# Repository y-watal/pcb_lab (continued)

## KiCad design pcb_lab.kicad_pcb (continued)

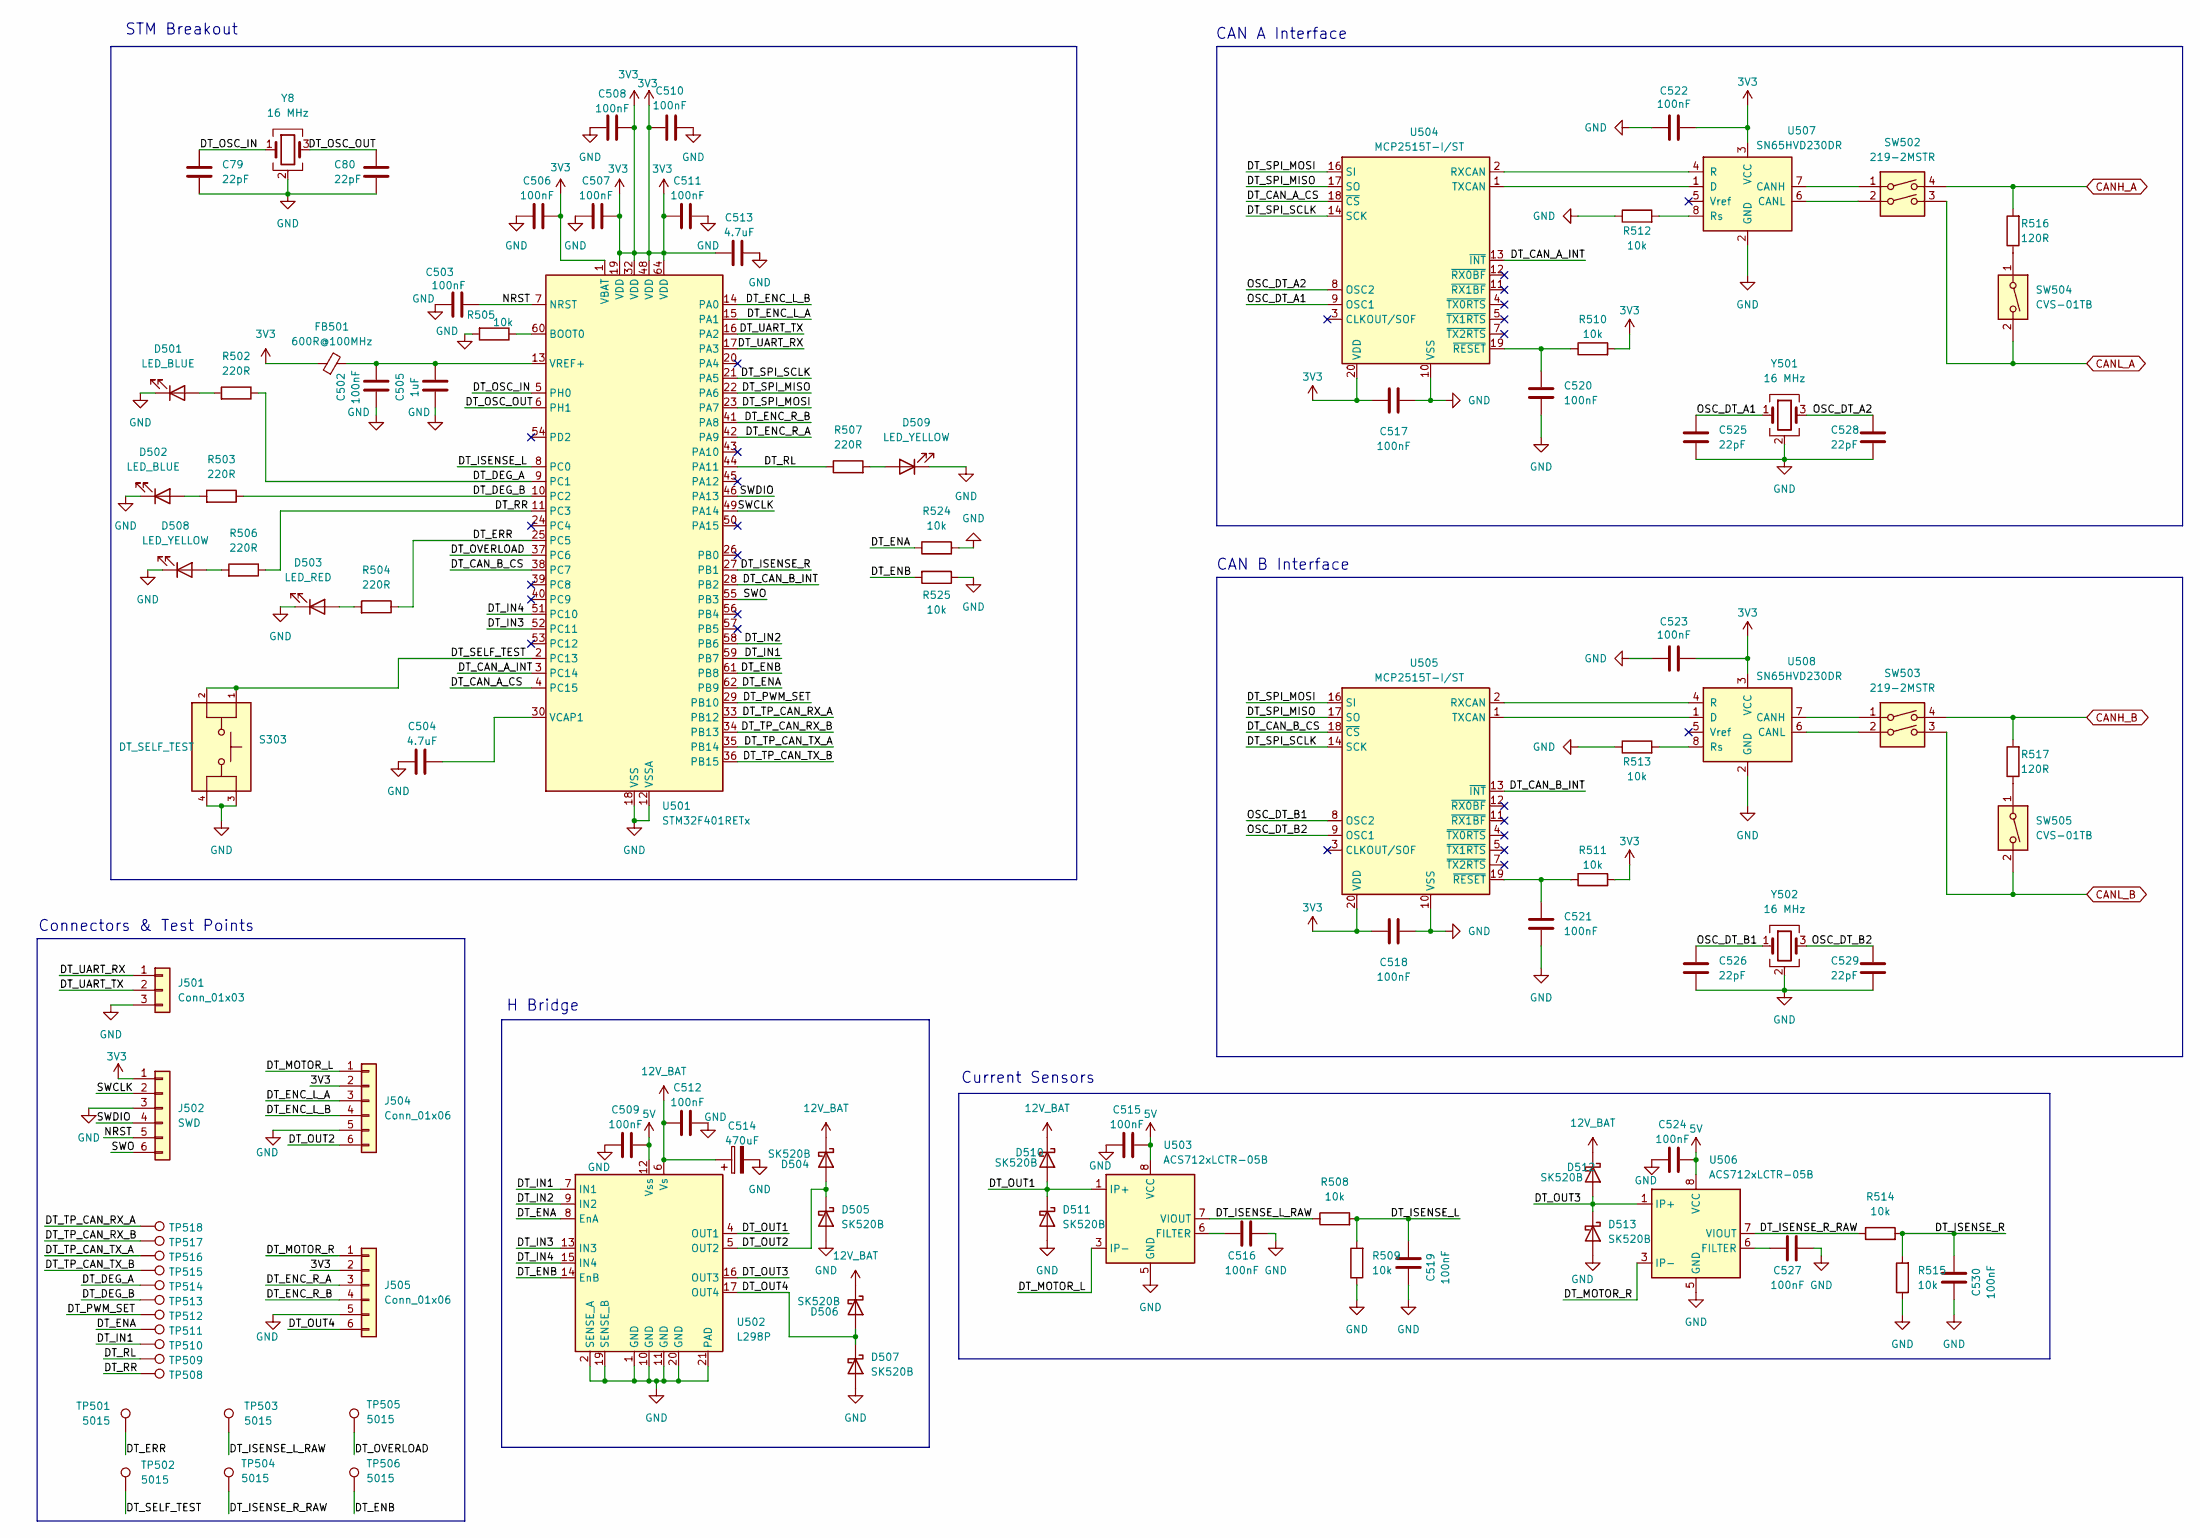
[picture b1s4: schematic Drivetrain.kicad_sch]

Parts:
C79, C80, C525, C526, C528, C529: 22pF; C_0603_1608Metric; Manufacturer Part Number C0603C220J1GACTU; LCSC Part # C2168649
C502, C503, C506, C507, C508, C509, C510, C511, C512, C515, C516, C517, C518, C519, C520, C521, C522, C523, C524, C527, C530: 100nF; C_0603_1608Metric; Manufacturer Part Number C0603C104K3RACAUTO; LCSC Part # C172738
C504, C513: 4.7uF; C_0805_2012Metric; Manufacturer Part Number GRM219R61E475KA73D
C505: 1uF; C_0603_1608Metric; Manufacturer Part Number CL10A105KB8NNNC; LCSC Part # C15849
C514: 470uF; CP_Radial_D8.0mm_P3.50mm; Manufacturer Part Number 860020474014
D501, D502: LED_BLUE; LED_D3.0mm; Manufacturer Part Number 151033BS03000
D503: LED_RED; LED_D3.0mm; Manufacturer Part Number 151031SS06000; LCSC Part # C6067185
D504, D505, D506, D507, D510, D511, D512, D513: SK520B; D_SMB; Manufacturer Part Number SK520B; LCSC Part # C139681
D508, D509: LED_YELLOW; LED_D3.0mm; Manufacturer Part Number 151031YS06000
FB501: 600R@100MHz; L_0603_1608Metric; Manufacturer Part Number 742863160
J501: Conn_01x03; PinHeader_1x03_P2.54mm_Vertical; Manufacturer Part Number TSW-103-07-G-S
J502: SWD; PinHeader_1x06_P2.54mm_Vertical; Manufacturer Part Number TSW-106-07-G-S
J504, J505: Conn_01x06; JST_PH_B6B-PH-SM4-TB_1x06-1MP_P2.00mm_Vertical; Manufacturer Part Number B6B-PH-SM4-TB(LF)(SN); LCSC Part # C471518
R502, R503, R504, R506, R507: 220R; R_0603_1608Metric; Manufacturer Part Number CRCW0603220RFKEA; LCSC Part # C844757
R505, R508, R509, R510, R511, R512, R513, R514, R515, R524, R525: 10k; R_0603_1608Metric; Manufacturer Part Number CRCW060310K0FKEA; LCSC Part # C844918
R516, R517: 120R; R_0603_1608Metric; Manufacturer Part Number RC0603FR-07120RL; LCSC Part # C114640
S303: DT_SELF_TEST; SW_SWT0210-045026GSA_REVA; Manufacturer Part Number SWT0210-045026GSA
SW502, SW503: 219-2MSTR; SW_DIP_SPSTx02_Slide_6.7x6.64mm_W8.61mm_P2.54mm_LowProfile; Manufacturer Part Number 219-2MSTR; LCSC Part # C2961978
SW504, SW505: CVS-01TB; SW_DIP_SPSTx01_Slide_Copal_CVS-01xB_W5.9mm_P1mm; Manufacturer Part Number CVS-01TB; LCSC Part # C2921743
TP501, TP502, TP503, TP504, TP505, TP506, TP508, TP509, TP510, TP511, TP512, TP513, TP514, TP515, TP516, TP517, TP518: 5015; TestPoint_Keystone_5015_Micro_Mini; Manufacturer Part Number 5015; LCSC Part # C2906768
U501: STM32F401RETx; LQFP-64_10x10mm_P0.5mm; Manufacturer Part Number STM32F401RET6; LCSC Part # C116978
U502: L298P; HSOP-20-1EP_11.0x15.9mm_P1.27mm_SlugDown; Manufacturer Part Number L298P013TR; LCSC Part # C111210
U503, U506: ACS712xLCTR-05B; SOIC-8_3.9x4.9mm_P1.27mm; Manufacturer Part Number ACS712ELCTR-05B-T; LCSC Part # C44471
U504, U505: MCP2515T-I/ST; TSSOP-20_4.4x6.5mm_P0.65mm; Manufacturer Part Number MCP2515T-I/ST; LCSC Part # C185941
U507, U508: SN65HVD230DR; SOIC-8_3.9x4.9mm_P1.27mm; Manufacturer Part Number SN65HVD230DR; LCSC Part # C12084
Y8, Y501, Y502: 16 MHz; Crystal_SMD_3225-4Pin_3.2x2.5mm; Manufacturer Part Number CX3225SB16000H0FLJCC

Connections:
3V3: C506.2, C507.2, C508.2, C510.1, C511.1, C513.1, C517.1, C518.1, C522.1, C523.1, FB501.1, J502.1, J504.2, J505.2, R510.2, R511.2, U501.1 (VBAT), U501.19 (VDD), U501.32 (VDD), U501.48 (VDD), U501.64 (VDD), U504.20 (VDD), U505.20 (VDD), U507.3 (VCC), U508.3 (VCC); also elsewhere on the board
5V: C509.2, C515.2, C524.2, U502.12 (Vss), U503.8 (VCC), U506.8 (VCC); also elsewhere on the board
12V_BAT: C512.1, C514.1, D504.1 (K), D506.1 (K), D510.1 (K), D512.1 (K), U502.6 (Vs); also elsewhere on the board
/Drivetrain/DT_CAN_A_CS: U501.4 (PC15), U504.18 (~CS)
/Drivetrain/DT_CAN_A_INT: U501.3 (PC14), U504.13 (~INT)
/Drivetrain/DT_CAN_B_CS: U501.38 (PC7), U505.18 (~CS)
/Drivetrain/DT_CAN_B_INT: U501.28 (PB2), U505.13 (~INT)
/Drivetrain/DT_DEG_A: R502.1, TP514.1 (1_1), U501.9 (PC1)
/Drivetrain/DT_DEG_B: R503.1, TP513.1 (1_1), U501.10 (PC2)
/Drivetrain/DT_ENA: R524.1, TP511.1 (1_1), U501.62 (PB9), U502.8 (EnA)
/Drivetrain/DT_ENB: R525.2, TP506.1 (1_1), U501.61 (PB8), U502.14 (EnB)
/Drivetrain/DT_ENC_L_A: J504.3, U501.15 (PA1)
/Drivetrain/DT_ENC_L_B: J504.4, U501.14 (PA0)
/Drivetrain/DT_ENC_R_A: J505.3, U501.42 (PA9)
/Drivetrain/DT_ENC_R_B: J505.4, U501.41 (PA8)
/Drivetrain/DT_ERR: R504.1, TP501.1 (1_1), U501.25 (PC5)
/Drivetrain/DT_IN1: TP510.1 (1_1), U501.59 (PB7), U502.7 (IN1)
/Drivetrain/DT_IN2: U501.58 (PB6), U502.9 (IN2)
/Drivetrain/DT_IN3: U501.52 (PC11), U502.13 (IN3)
/Drivetrain/DT_IN4: U501.51 (PC10), U502.15 (IN4)
/Drivetrain/DT_ISENSE_L: C519.2, R508.2, R509.2, U501.8 (PC0)
/Drivetrain/DT_ISENSE_L_RAW: R508.1, TP503.1 (1_1), U503.7 (VIOUT)
/Drivetrain/DT_ISENSE_R: C530.2, R514.2, R515.2, U501.27 (PB1)
/Drivetrain/DT_ISENSE_R_RAW: R514.1, TP504.1 (1_1), U506.7 (VIOUT)
/Drivetrain/DT_MOTOR_L: J504.1, U503.3 (IP-), U503.4 (IP-)
/Drivetrain/DT_MOTOR_R: J505.1, U506.3 (IP-), U506.4 (IP-)
/Drivetrain/DT_OSC_IN: C79.1, U501.5 (PH0), Y8.1
/Drivetrain/DT_OSC_OUT: C80.1, U501.6 (PH1), Y8.3
/Drivetrain/DT_OUT1: D510.2 (A), D511.1 (K), U502.4 (OUT1), U503.1 (IP+), U503.2 (IP+)
/Drivetrain/DT_OUT2: D504.2 (A), D505.1 (K), J504.6, U502.5 (OUT2)
/Drivetrain/DT_OUT3: D512.2 (A), D513.1 (K), U502.16 (OUT3), U506.1 (IP+), U506.2 (IP+)
/Drivetrain/DT_OUT4: D506.2 (A), D507.1 (K), J505.6, U502.17 (OUT4)
/Drivetrain/DT_OVERLOAD: TP505.1 (1_1), U501.37 (PC6)
/Drivetrain/DT_PWM_SET: TP512.1 (1_1), U501.29 (PB10)
/Drivetrain/DT_RL: R507.1, TP509.1 (1_1), U501.44 (PA11)
/Drivetrain/DT_RR: R506.1, TP508.1 (1_1), U501.11 (PC3)
/Drivetrain/DT_SELF_TEST: S303.1, S303.2, TP502.1 (1_1), U501.2 (PC13)
/Drivetrain/DT_SPI_MISO: U501.22 (PA6), U504.17 (SO), U505.17 (SO)
/Drivetrain/DT_SPI_MOSI: U501.23 (PA7), U504.16 (SI), U505.16 (SI)
/Drivetrain/DT_SPI_SCLK: U501.21 (PA5), U504.14 (SCK), U505.14 (SCK)
/Drivetrain/DT_TP_CAN_RX_A: TP518.1 (1_1), U501.33 (PB12)
/Drivetrain/DT_TP_CAN_RX_B: TP517.1 (1_1), U501.34 (PB13)
/Drivetrain/DT_TP_CAN_TX_A: TP516.1 (1_1), U501.35 (PB14)
/Drivetrain/DT_TP_CAN_TX_B: TP515.1 (1_1), U501.36 (PB15)
/Drivetrain/DT_UART_RX: J501.1, U501.17 (PA3)
/Drivetrain/DT_UART_TX: J501.2, U501.16 (PA2)
/Drivetrain/NRST: C503.2, J502.5, U501.7 (NRST)
/Drivetrain/OSC_DT_A1: C525.1, U504.9 (OSC1), Y501.1
/Drivetrain/OSC_DT_A2: C528.1, U504.8 (OSC2), Y501.3
/Drivetrain/OSC_DT_B1: C526.1, U505.8 (OSC2), Y502.1
/Drivetrain/OSC_DT_B2: C529.1, U505.9 (OSC1), Y502.3
/Drivetrain/SWCLK: J502.2, U501.49 (PA14)
/Drivetrain/SWDIO: J502.4, U501.46 (PA13)
/Drivetrain/SWO: J502.6, U501.55 (PB3)
CANH_A: R516.2, SW502.4; also elsewhere on the board
CANH_B: R517.2, SW503.4; also elsewhere on the board
CANL_A: SW502.3, SW504.2; also elsewhere on the board
CANL_B: SW503.3, SW505.2; also elsewhere on the board
GND: C79.2, C80.2, C502.1, C503.1, C504.1, C505.1, C506.1, C507.1, C508.1, C509.1, C510.2, C511.2, C512.2, C513.2, C514.2, C515.1, C516.2, C517.2, C518.2, C519.1, C520.2, C521.2, C522.2, C523.2, C524.1, C525.2, C526.2, C527.2, C528.2, C529.2, C530.1, D501.1 (K), D502.1 (K), D503.1 (K), D505.2 (A), D507.2 (A), D508.1 (K), D509.1 (K), D511.2 (A), D513.2 (A), J501.3, J502.3, J504.5, J505.5, R505.2, R509.1, R512.1, R513.1, R515.1, R524.2, R525.1, S303.3, S303.4, U501.12 (VSSA), U501.18 (VSS), U501.31 (VSS), U501.47 (VSS), U501.63 (VSS), U502.1 (GND), U502.2 (SENSE_A), U502.10 (GND), U502.11 (GND), U502.19 (SENSE_B), U502.20 (GND), U502.21 (PAD), U503.5 (GND), U504.10 (VSS), U505.10 (VSS), U506.5 (GND), U507.2 (GND), U508.2 (GND), Y8.2 (G), Y8.4 (G), Y501.2 (G), Y501.4 (G), Y502.2 (G), Y502.4 (G); also elsewhere on the board
unnamed: D501.2 (A), R502.2
unnamed: D502.2 (A), R503.2
unnamed: D503.2 (A), R504.2
unnamed: D508.2 (A), R506.2
unnamed: D509.2 (A), R507.2
unnamed: R516.1, SW504.1
unnamed: R517.1, SW505.1
unnamed: R505.1, U501.60 (BOOT0)
unnamed: C504.2, U501.30 (VCAP1)
unnamed: C502.2, C505.2, FB501.2, U501.13 (VREF+)
unnamed: C516.1, U503.6 (FILTER)
unnamed: U504.2 (RXCAN), U507.4 (R)
unnamed: U504.1 (TXCAN), U507.1 (D)
unnamed: C520.1, R510.1, U504.19 (~RESET)
unnamed: U505.2 (RXCAN), U508.4 (R)
unnamed: U505.1 (TXCAN), U508.1 (D)
unnamed: C521.1, R511.1, U505.19 (~RESET)
unnamed: C527.1, U506.6 (FILTER)
unnamed: SW502.1, U507.7 (CANH)
unnamed: SW502.2, U507.6 (CANL)
unnamed: R512.2, U507.8 (Rs)
unnamed: SW503.1, U508.7 (CANH)
unnamed: SW503.2, U508.6 (CANL)
unnamed: R513.2, U508.8 (Rs)

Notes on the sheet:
CAN A Interface
CAN B Interface
Connectors & Test Points
STM Breakout
H Bridge
Current Sensors

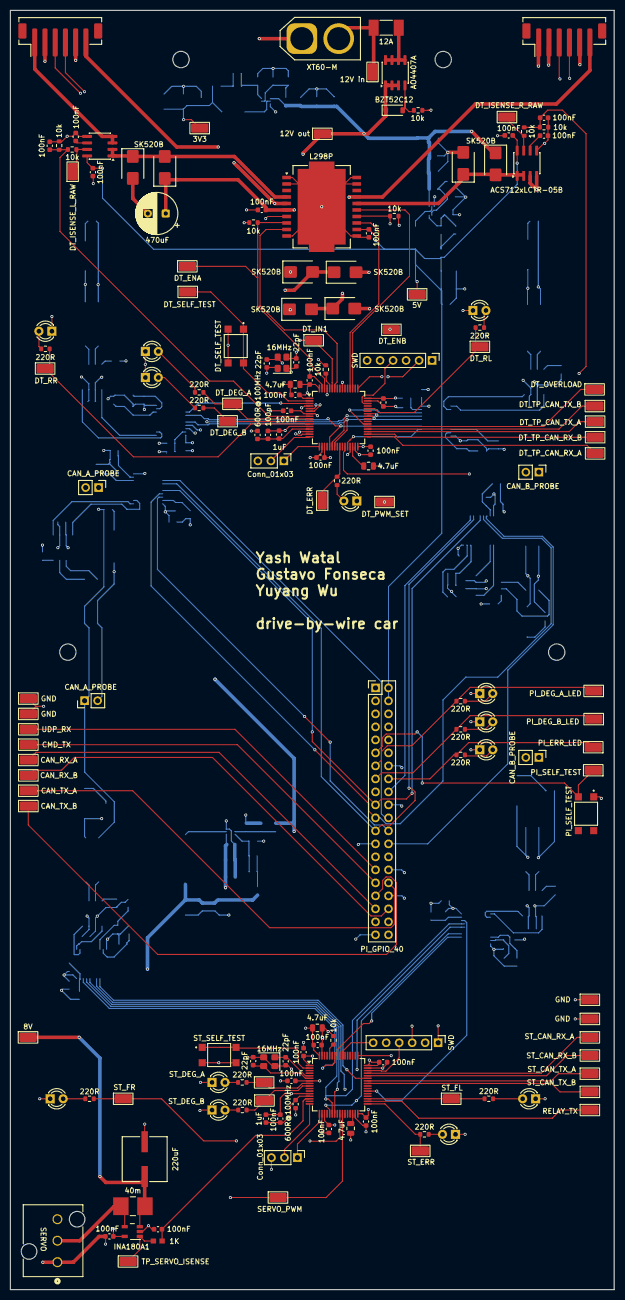
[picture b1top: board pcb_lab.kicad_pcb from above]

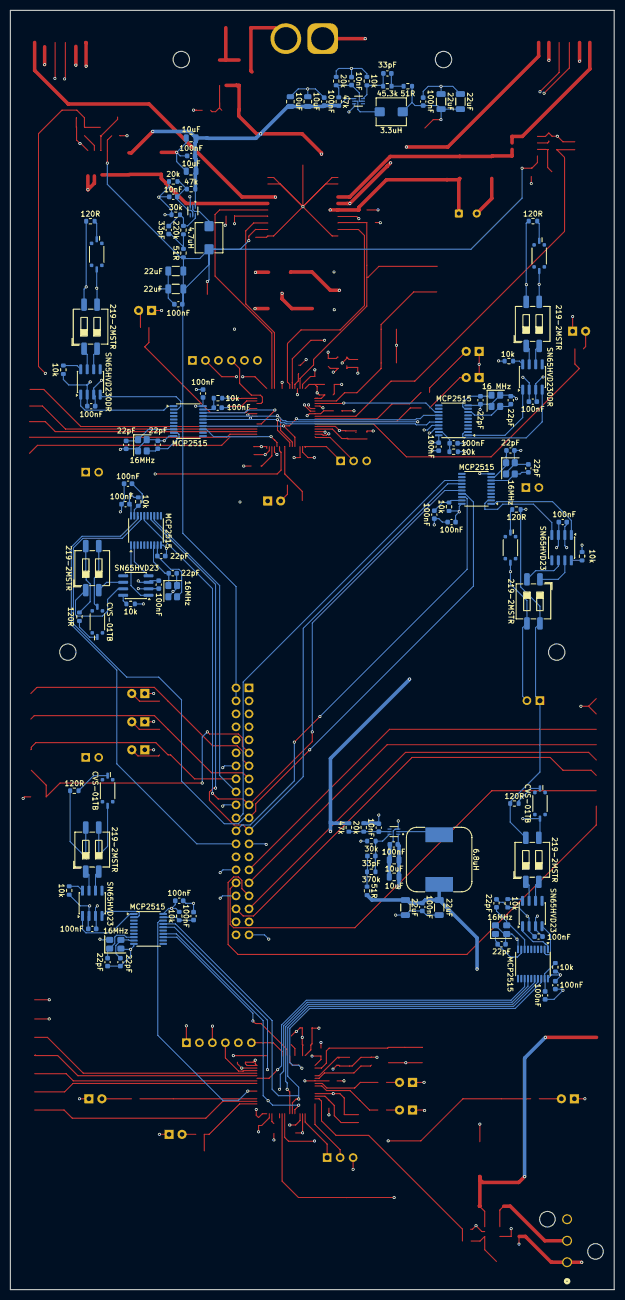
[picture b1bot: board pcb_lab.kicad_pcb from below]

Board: 4 copper layers, 118.0 x 250.0 mm, 285 parts (123 on the bottom side), 193 nets.

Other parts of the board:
J506: CAN_A_PROBE; PinHeader_1x02_P2.54mm_Vertical
J507: CAN_B_PROBE; PinHeader_1x02_P2.54mm_Vertical

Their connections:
CANH_A: J506.1; also elsewhere on the board
CANH_B: J507.1; also elsewhere on the board
CANL_A: J506.2; also elsewhere on the board
CANL_B: J507.2; also elsewhere on the board
